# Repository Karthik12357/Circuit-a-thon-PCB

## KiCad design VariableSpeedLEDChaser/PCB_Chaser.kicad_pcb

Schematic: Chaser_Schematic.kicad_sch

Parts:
C1: 33u; C_Radial_D6.3mm_H5.0mm_P2.50mm
D1, D2, D3, D4, D5, D6, D7, D8, D9, D10, D11: LED; LED_D5.0mm_Clear
J1: Screw_Terminal_01x02; TerminalBlock_RND_205-00012_1x02_P5.00mm_Horizontal
R1: 1k; R_Axial_DIN0207_L6.3mm_D2.5mm_P10.16mm_Horizontal
R2, R3, R4, R5, R6, R7, R8, R9, R10, R11, R12: 330; R_Axial_DIN0207_L6.3mm_D2.5mm_P10.16mm_Horizontal
RV1: 100k; Potentiometer_ACP_CA9-H5_Horizontal
U1: NE555P; DIP-8_W7.62mm
U2: 4017; DIP-16_W7.62mm_Socket

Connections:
/Out: R12.2, U1.3 (Q), U2.14 (CLK)
/Trig: C1.1, RV1.2, U1.2 (TR), U1.6 (THR)
/Vcc: J1.2, R1.1, U1.4 (R), U1.8 (VCC), U2.16 (VDD)
GND: C1.2, D1.1 (K), D2.1 (K), D3.1 (K), D4.1 (K), D5.1 (K), D6.1 (K), D7.1 (K), D8.1 (K), D9.1 (K), D10.1 (K), D11.1 (K), J1.1, RV1.1, U1.1 (GND), U2.8 (VSS), U2.13 (CKEN), U2.15 (Reset)
unnamed: D1.2 (A), R2.2
unnamed: D2.2 (A), R3.2
unnamed: D3.2 (A), R4.2
unnamed: D4.2 (A), R5.2
unnamed: D5.2 (A), R6.2
unnamed: D6.2 (A), R7.2
unnamed: D7.2 (A), R8.2
unnamed: D8.2 (A), R9.2
unnamed: D9.2 (A), R10.2
unnamed: D10.2 (A), R11.2
unnamed: D11.2 (A), R12.1
unnamed: R1.2, RV1.3, U1.7 (DIS)
unnamed: R2.1, U2.3 (Q0)
unnamed: R3.1, U2.2 (Q1)
unnamed: R4.1, U2.4 (Q2)
unnamed: R5.1, U2.7 (Q3)
unnamed: R6.1, U2.10 (Q4)
unnamed: R7.1, U2.1 (Q5)
unnamed: R8.1, U2.5 (Q6)
unnamed: R9.1, U2.6 (Q7)
unnamed: R10.1, U2.9 (Q8)
unnamed: R11.1, U2.11 (Q9)

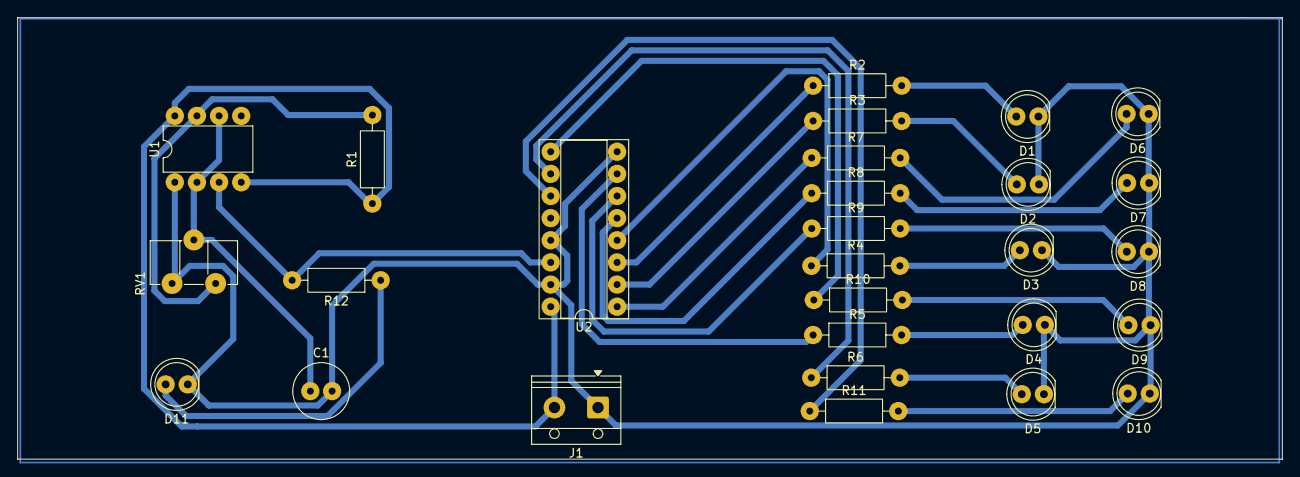
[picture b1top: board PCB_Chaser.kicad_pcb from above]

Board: 2 copper layers, 145.1 x 50.7 mm, 28 parts (0 on the bottom side), 26 nets.

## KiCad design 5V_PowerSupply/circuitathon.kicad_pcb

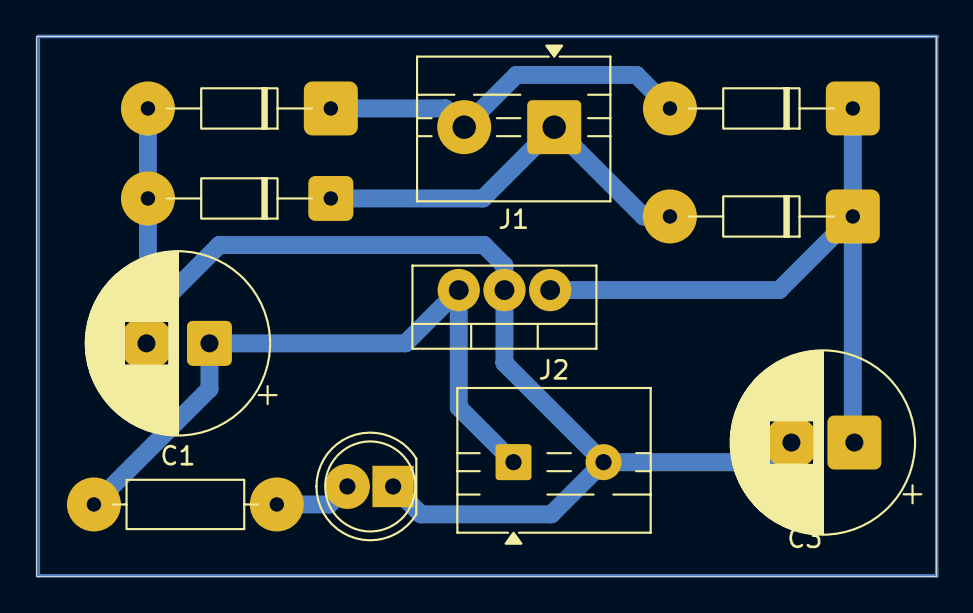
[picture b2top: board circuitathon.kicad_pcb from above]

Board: 2 copper layers, 50.0 x 30.0 mm, 11 parts (0 on the bottom side), 6 nets.

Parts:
C1: CAP; CP_Radial_D10.0mm_P3.50mm
C3: 470uF; CP_Radial_D10.0mm_P3.50mm
D1, D2, D3, D4: 1N4148WT; D_DO-35_SOD27_P10.16mm_Horizontal
D5: LED; LED_D5.0mm_Clear
J1, J2: Screw_Terminal_01x02; TerminalBlock_MaiXu_MX126-5.0-02P_1x02_P5.00mm
R1: 330Ω; R_Axial_DIN0207_L6.3mm_D2.5mm_P10.16mm_Horizontal
U1: LM7805_TO220; TO-220-3_Vertical

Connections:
/+5V: C1.1, J2.1, R1.2, U1.3 (VO)
GND: C1.2, C3.2, D1.2 (A), D3.2 (A), D5.1 (K), J2.2, U1.2 (GND)
unnamed: D1.1 (K), D2.2 (A), J1.2
unnamed: C3.1, D2.1 (K), D4.1 (K), U1.1 (VI)
unnamed: D3.1 (K), D4.2 (A), J1.1
unnamed: D5.2 (A), R1.1

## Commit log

2025-12-11 Create 5V
2025-12-11 Create schematic
